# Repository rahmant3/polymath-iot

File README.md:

# Polymath-IoT

This project is a submission for the Climate Change Challenge hosted by Quicklogic Corp.: https://www.quicklogic.com/climate-change-challenge/

## Overview

Polymath-IoT is a generic sensor cluster consisting of two separate modules that connect together, a controller module and sensor module. The module is intended to be attached to a room and passively collect and publish data over BLE.

The controller module consists of a two-micro system, with the slave system acting as an IO expander, and the master module collecting the data and publishing it over BLE.

The sensor module simply contains all of the sensors for a particular sensor cluster, and connects to the controller module. For this competition our focus was on creating a sensor cluster for collecting air quality data.

## Directory Structure
- hardware -- Contains the schematic for the Polymath system, as well as the files needed to build the PCB for the system.
- quickfeather -- Contains the documentation and source code for the master controller of the Polymath system, hosted on a Quickfeather board.
- stm32 -- Contains the documentation and source code for the slave controller of the Polymath system, hosted on an STM32 micro.
- utils -- Contains utility scripts used to support this project, such as Python scripts used to obtain training data from the system over BLE.

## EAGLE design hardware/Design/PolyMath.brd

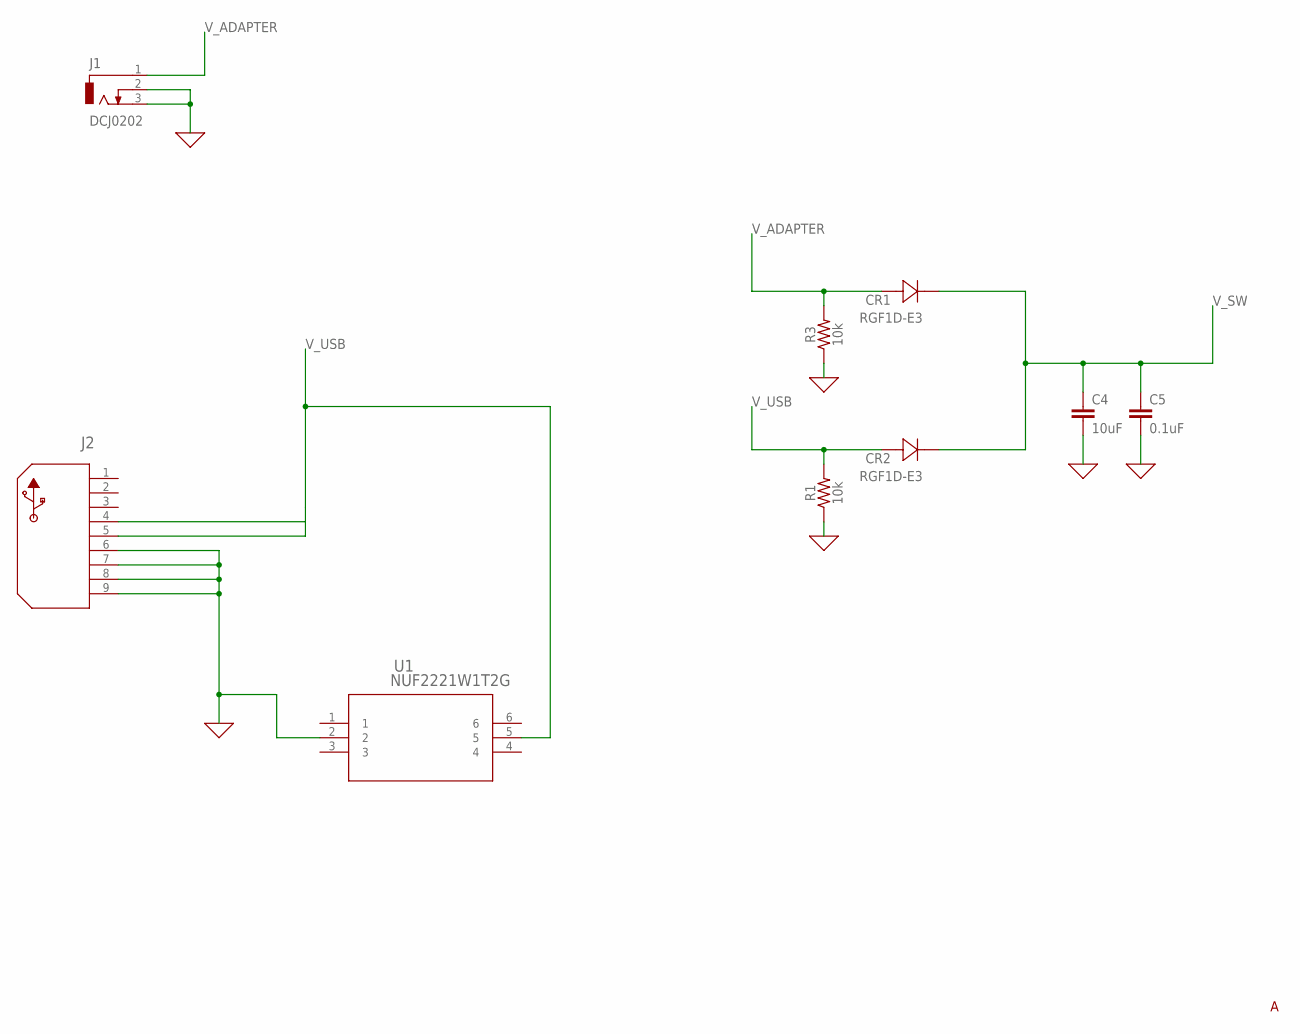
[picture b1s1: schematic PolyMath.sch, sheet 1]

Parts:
C4: 10uF; 0603
C5: 0.1uF; 0603
CR1, CR2: RGF1D-E3; DIODE_DO214BA
J1: DCJ0202
J2: 1734035-4; CONN5_USB1734035_TEC
R1, R3: 10k; 0603
U1: NUF2221W1T2G; SOIC6_SC70_1P35X2P2_ONS

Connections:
0: C4.2, C5.2, J1.2, J1.3, J2.6, J2.7, J2.8, J2.9, R1.1, R3.1, U1.2; also elsewhere on the board
V_ADAPTER: CR1.2, J1.1, R3.2
V_SW: C4.1, C5.1, CR1.1, CR2.1; also elsewhere on the board
V_USB: CR2.2, J2.4, J2.5, R1.2, U1.5

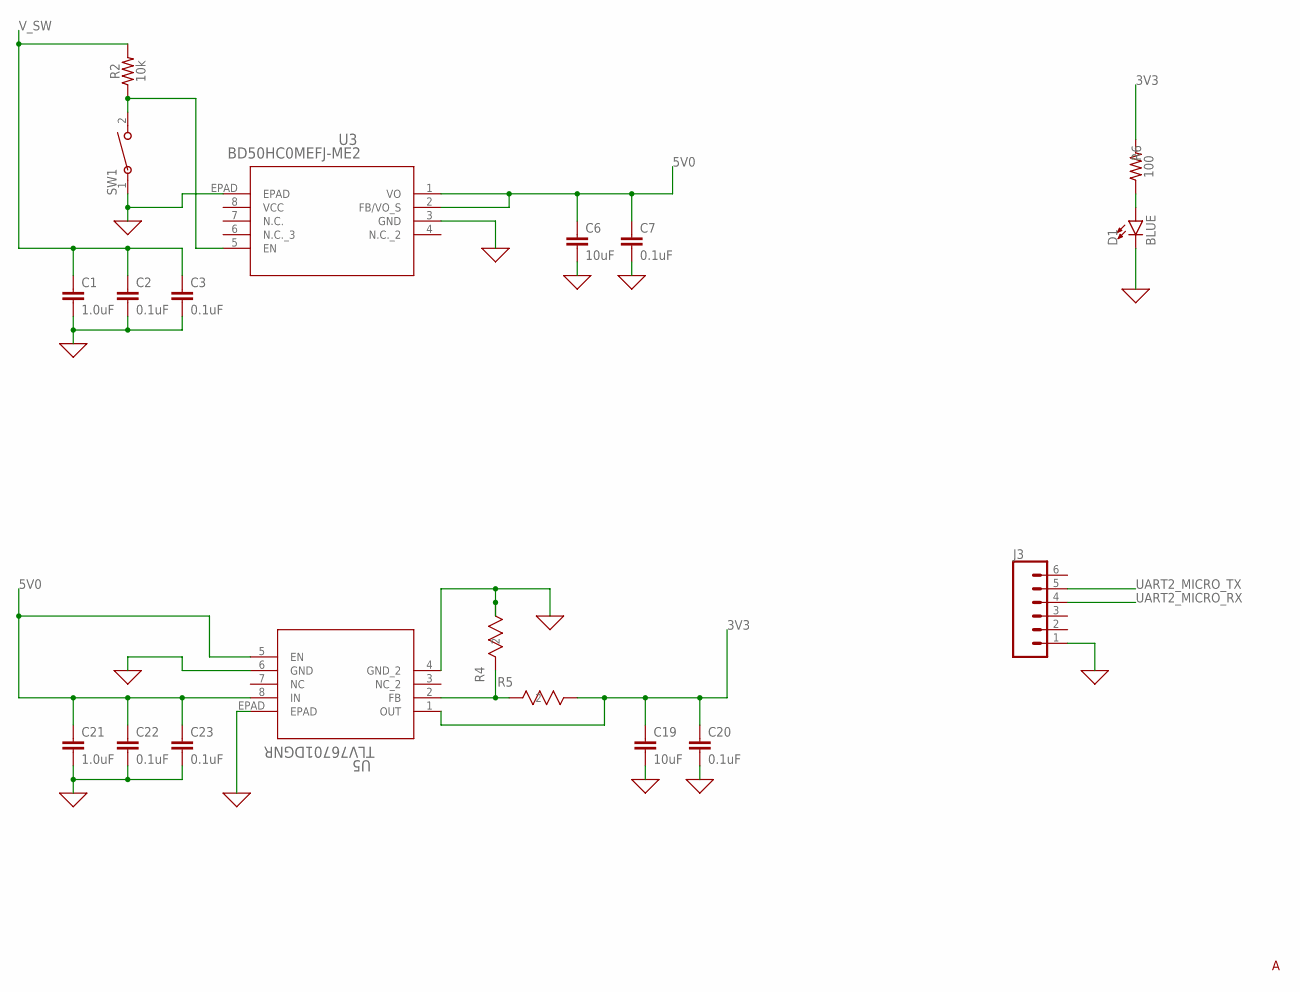
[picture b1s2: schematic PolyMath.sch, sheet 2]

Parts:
C1, C21: 1.0uF; 0603
C2, C3, C7, C20, C22, C23: 0.1uF; 0603
C6, C19: 10uF; 0603
D1: BLUE; LED-0603
J3: CONN_06NO_SILK_FEMALE_PTH; 1X06_NO_SILK
R2: 10k; 0603
R4: TNPW0603160KBEEA; RC0603N_VIS
R5: CRCW0603499KFKEA; RES_CRCW_0603
R6: 100; 0603
SW1: TL9320AF400QG; SW_TL9320_EWI
U3: BD50HC0MEFJ-ME2; HTSOP-J8_ROM
U5: TLV76701DGNR; SOIC_01DGNR_TEX

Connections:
0: C1.2, C2.2, C3.2, C6.2, C7.2, C19.2, C20.2, C21.2, C22.2, C23.2, D1.C, J3.1, R4.1, SW1.1, U3.3 (GND), U3.EPAD, U5.4 (GND_2), U5.6 (GND), U5.EPAD; also elsewhere on the board
3V3: C19.1, C20.1, R5.1, R6.2, U5.1 (OUT); also elsewhere on the board
5V0: C6.1, C7.1, C21.1, C22.1, C23.1, U3.1 (VO), U3.2 (FB/VO_S), U5.5 (EN), U5.8 (IN); also elsewhere on the board
unnamed: R2.1, SW1.2, U3.5 (EN)
unnamed: D1.A, R6.1
unnamed: R4.2, R5.2, U5.2 (FB)
UART2_MICRO_RX: J3.4; also elsewhere on the board
UART2_MICRO_TX: J3.5; also elsewhere on the board
VCC: U3.8 (VCC)
V_SW: C1.1, C2.1, C3.1, R2.2; also elsewhere on the board

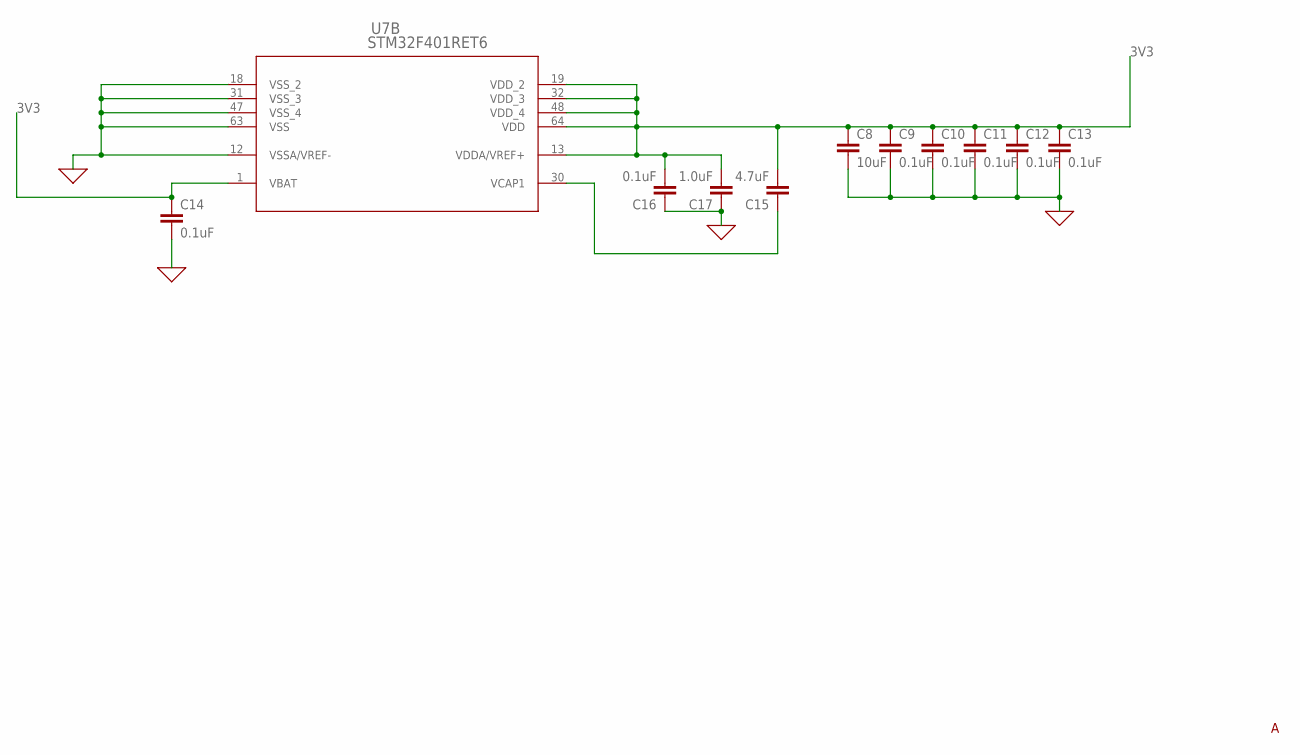
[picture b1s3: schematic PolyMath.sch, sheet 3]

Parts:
C8: 10uF; 0805
C9, C10, C11, C12, C13, C14, C16: 0.1uF; 0603
C15: 4.7uF; 0603
C17: 1.0uF; 0805
U7: STM32F401RET6; LQFP64-10X10MM

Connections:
0: C8.2, C9.2, C10.2, C11.2, C12.2, C13.2, C14.2, C16.1, C17.1, U7.12 (VSSA/VREF-), U7.18 (VSS_2), U7.31 (VSS_3), U7.47 (VSS_4), U7.63 (VSS); also elsewhere on the board
3V3: C8.1, C9.1, C10.1, C11.1, C12.1, C13.1, C14.1, C15.2, C16.2, C17.2, U7.1 (VBAT), U7.13 (VDDA/VREF+), U7.19 (VDD_2), U7.32 (VDD_3), U7.48 (VDD_4), U7.64 (VDD); also elsewhere on the board
unnamed: C15.1, U7.30 (VCAP1)

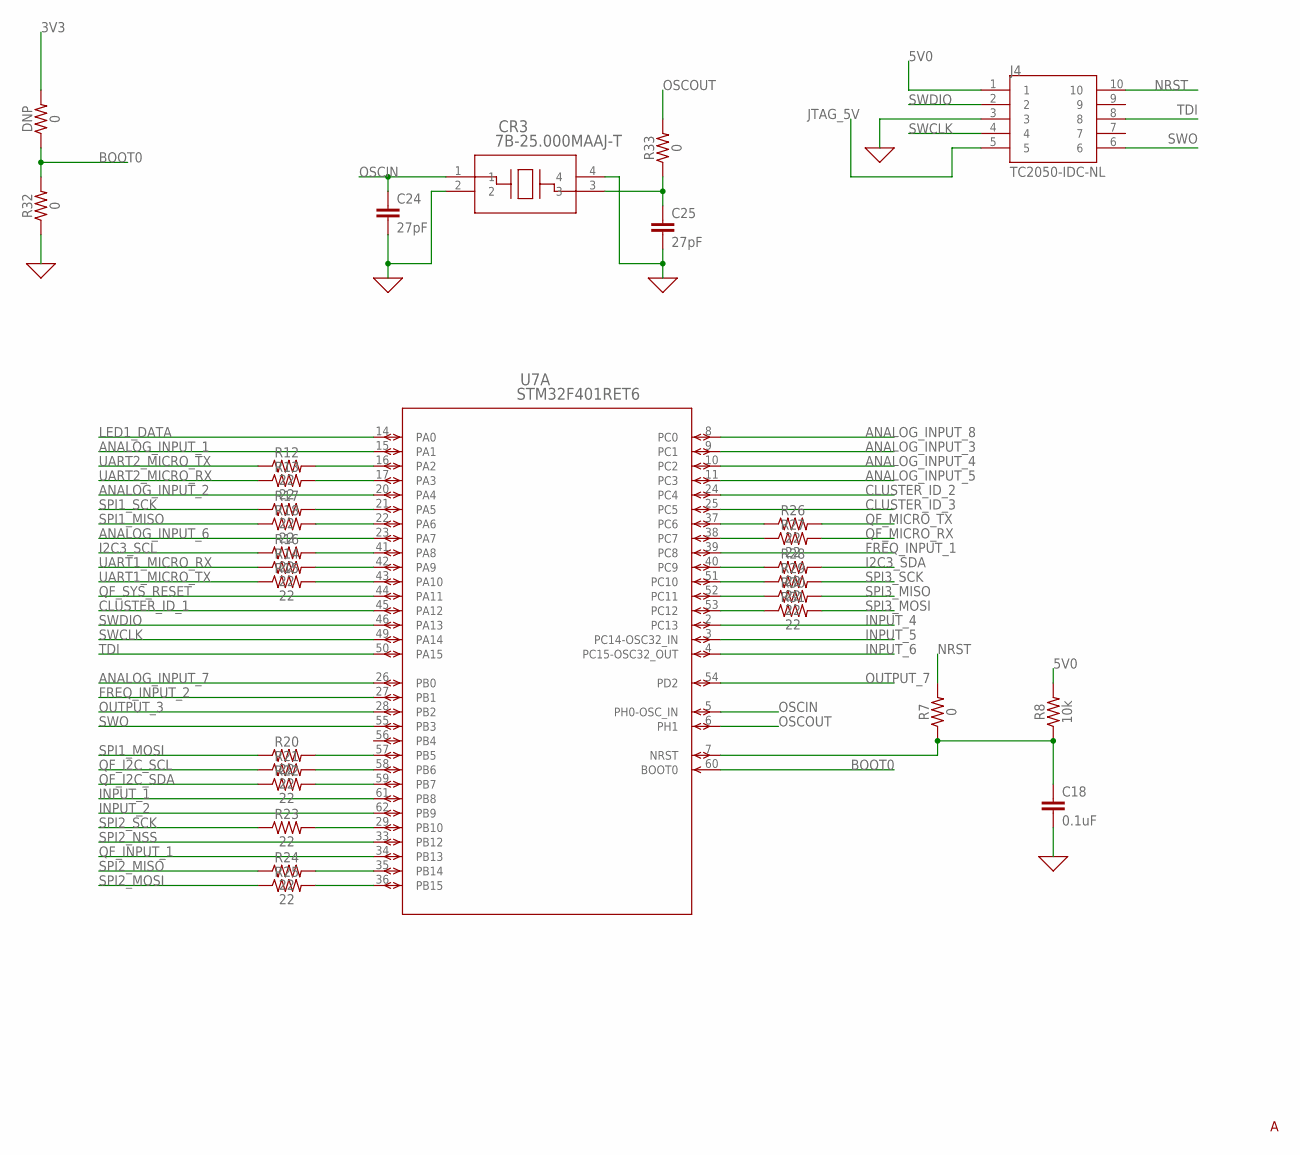
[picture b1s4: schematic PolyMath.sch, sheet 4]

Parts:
C18: 0.1uF; 0603
C24, C25: 27pF; 0603
CR3: 7B-25.000MAAJ-T; CRYSTAL_TXC_7B
DNP: 0; 0603
J4: TC2050-IDC-NL; TAG-CONNECT_TC2050-IDC-NL
R7, R32, R33: 0; 0603
R8: 10k; 0603
R12, R13, R14, R15, R16, R17, R18, R20, R21, R22, R23, R24, R25, R26, R27, R28, R29, R30, R31: 22; 0402
U7: STM32F401RET6; LQFP64-10X10MM

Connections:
0: C18.2, C24.2, C25.2, CR3.2, CR3.4, J4.3, R32.1; also elsewhere on the board
3V3: DNP.2; also elsewhere on the board
5V0: J4.1; also elsewhere on the board
ANALOG_INPUT_1: U7.15 (PA1); also elsewhere on the board
ANALOG_INPUT_2: U7.20 (PA4); also elsewhere on the board
ANALOG_INPUT_3: U7.9 (PC1); also elsewhere on the board
ANALOG_INPUT_4: U7.10 (PC2); also elsewhere on the board
ANALOG_INPUT_5: U7.11 (PC3); also elsewhere on the board
ANALOG_INPUT_6: U7.23 (PA7); also elsewhere on the board
ANALOG_INPUT_7: U7.26 (PB0); also elsewhere on the board
ANALOG_INPUT_8: U7.8 (PC0); also elsewhere on the board
BOOT0: DNP.1, R32.2, U7.60 (BOOT0)
CLUSTER_ID_1: U7.45 (PA12); also elsewhere on the board
CLUSTER_ID_2: U7.24 (PC4); also elsewhere on the board
CLUSTER_ID_3: U7.25 (PC5); also elsewhere on the board
FREQ_INPUT_1: U7.39 (PC8); also elsewhere on the board
FREQ_INPUT_2: U7.27 (PB1); also elsewhere on the board
I2C3_SCL: R16.1; also elsewhere on the board
I2C3_SDA: R28.2; also elsewhere on the board
INPUT_1: U7.61 (PB8); also elsewhere on the board
INPUT_2: U7.62 (PB9); also elsewhere on the board
INPUT_4: U7.2 (PC13); also elsewhere on the board
INPUT_5: U7.3 (PC14-OSC32_IN); also elsewhere on the board
INPUT_6: U7.4 (PC15-OSC32_OUT)
JTAG_5V: J4.5
LED1_DATA: U7.14 (PA0); also elsewhere on the board
unnamed: C18.1, R7.1, R8.1, U7.7 (NRST)
unnamed: C25.1, CR3.3, R33.1
unnamed: R12.2, U7.16 (PA2)
unnamed: R13.2, U7.17 (PA3)
unnamed: R14.2, U7.42 (PA9)
unnamed: R15.2, U7.43 (PA10)
unnamed: R16.2, U7.41 (PA8)
unnamed: R17.2, U7.21 (PA5)
unnamed: R18.2, U7.22 (PA6)
unnamed: R20.2, U7.57 (PB5)
unnamed: R21.2, U7.58 (PB6)
unnamed: R22.2, U7.59 (PB7)
unnamed: R23.2, U7.29 (PB10)
unnamed: R24.2, U7.35 (PB14)
unnamed: R25.2, U7.36 (PB15)
unnamed: R26.1, U7.37 (PC6)
unnamed: R27.1, U7.38 (PC7)
unnamed: R28.1, U7.40 (PC9)
unnamed: R29.1, U7.51 (PC10)
unnamed: R30.1, U7.52 (PC11)
unnamed: R31.1, U7.53 (PC12)
NRST: J4.10, R7.2
OSCIN: C24.1, CR3.1, U7.5 (PH0-OSC_IN)
OSCOUT: R33.2, U7.6 (PH1)
OUTPUT_3: U7.28 (PB2); also elsewhere on the board
OUTPUT_7: U7.54 (PD2); also elsewhere on the board
QF_I2C_SCL: R21.1; also elsewhere on the board
QF_I2C_SDA: R22.1; also elsewhere on the board
QF_INPUT_1: U7.34 (PB13); also elsewhere on the board
QF_MICRO_RX: R27.2; also elsewhere on the board
QF_MICRO_TX: R26.2; also elsewhere on the board
QF_SYS_RESET: U7.44 (PA11); also elsewhere on the board
SPI1_MISO: R18.1; also elsewhere on the board
SPI1_MOSI: R20.1; also elsewhere on the board
SPI1_SCK: R17.1; also elsewhere on the board
SPI2_MISO: R24.1; also elsewhere on the board
SPI2_MOSI: R25.1; also elsewhere on the board
SPI2_NSS: U7.33 (PB12); also elsewhere on the board
SPI2_SCK: R23.1; also elsewhere on the board
SPI3_MISO: R30.2; also elsewhere on the board
SPI3_MOSI: R31.2; also elsewhere on the board
SPI3_SCK: R29.2; also elsewhere on the board
SWCLK: J4.4, U7.49 (PA14)
SWDIO: J4.2, U7.46 (PA13)
SWO: J4.6, U7.55 (PB3)
TDI: J4.8, U7.50 (PA15)
UART1_MICRO_RX: R14.1; also elsewhere on the board
UART1_MICRO_TX: R15.1; also elsewhere on the board
UART2_MICRO_RX: R13.1; also elsewhere on the board
UART2_MICRO_TX: R12.1; also elsewhere on the board

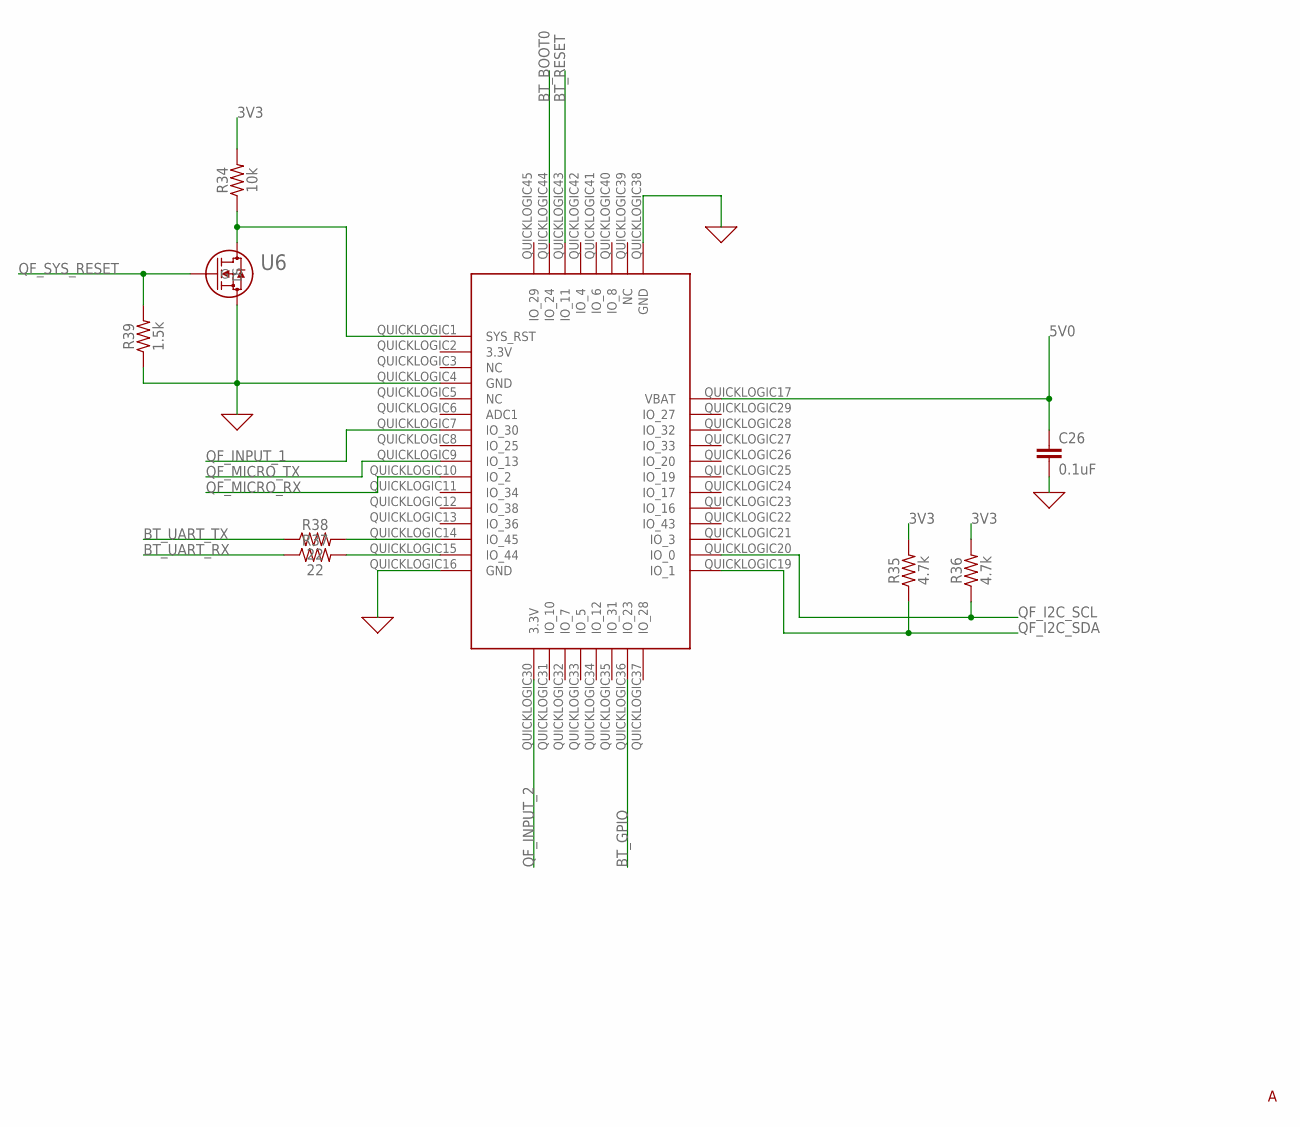
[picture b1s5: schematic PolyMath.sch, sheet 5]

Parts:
C26: 0.1uF; 0603
R34: 10k; 0603
R35, R36: 4.7k; 0603
R37, R38: 22; 0402
R39: 1.5k; 0603
U6: DMN65D8L-7SOT-23_2P9X1P3_DIO-M; SOT-23_2P9X1P3_DIO-M
U$1: QUICKFEATHER; QUICKLOGIC

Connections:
0: C26.2, R39.1, U6.3 (S), U$1.QUICKLOGIC4 (GND), U$1.QUICKLOGIC16 (GND), U$1.QUICKLOGIC38 (GND); also elsewhere on the board
3V3: R34.2, R35.2, R36.2; also elsewhere on the board
5V0: C26.1, U$1.QUICKLOGIC17 (VBAT); also elsewhere on the board
BT_BOOT0: U$1.QUICKLOGIC44 (IO_24); also elsewhere on the board
BT_GPIO: U$1.QUICKLOGIC36 (IO_23); also elsewhere on the board
BT_RESET: U$1.QUICKLOGIC43 (IO_11); also elsewhere on the board
BT_UART_RX: R37.1; also elsewhere on the board
BT_UART_TX: R38.1; also elsewhere on the board
unnamed: R34.1, U6.2 (D), U$1.QUICKLOGIC1 (SYS_RST)
unnamed: R38.2, U$1.QUICKLOGIC14 (IO_45)
unnamed: R37.2, U$1.QUICKLOGIC15 (IO_44)
QF_I2C_SCL: R36.1, U$1.QUICKLOGIC20 (IO_0); also elsewhere on the board
QF_I2C_SDA: R35.1, U$1.QUICKLOGIC19 (IO_1); also elsewhere on the board
QF_INPUT_1: U$1.QUICKLOGIC7 (IO_30); also elsewhere on the board
QF_INPUT_2: U$1.QUICKLOGIC30 (3.3V)
QF_MICRO_RX: U$1.QUICKLOGIC10 (IO_2); also elsewhere on the board
QF_MICRO_TX: U$1.QUICKLOGIC9 (IO_13); also elsewhere on the board
QF_SYS_RESET: R39.2, U6.1 (G); also elsewhere on the board

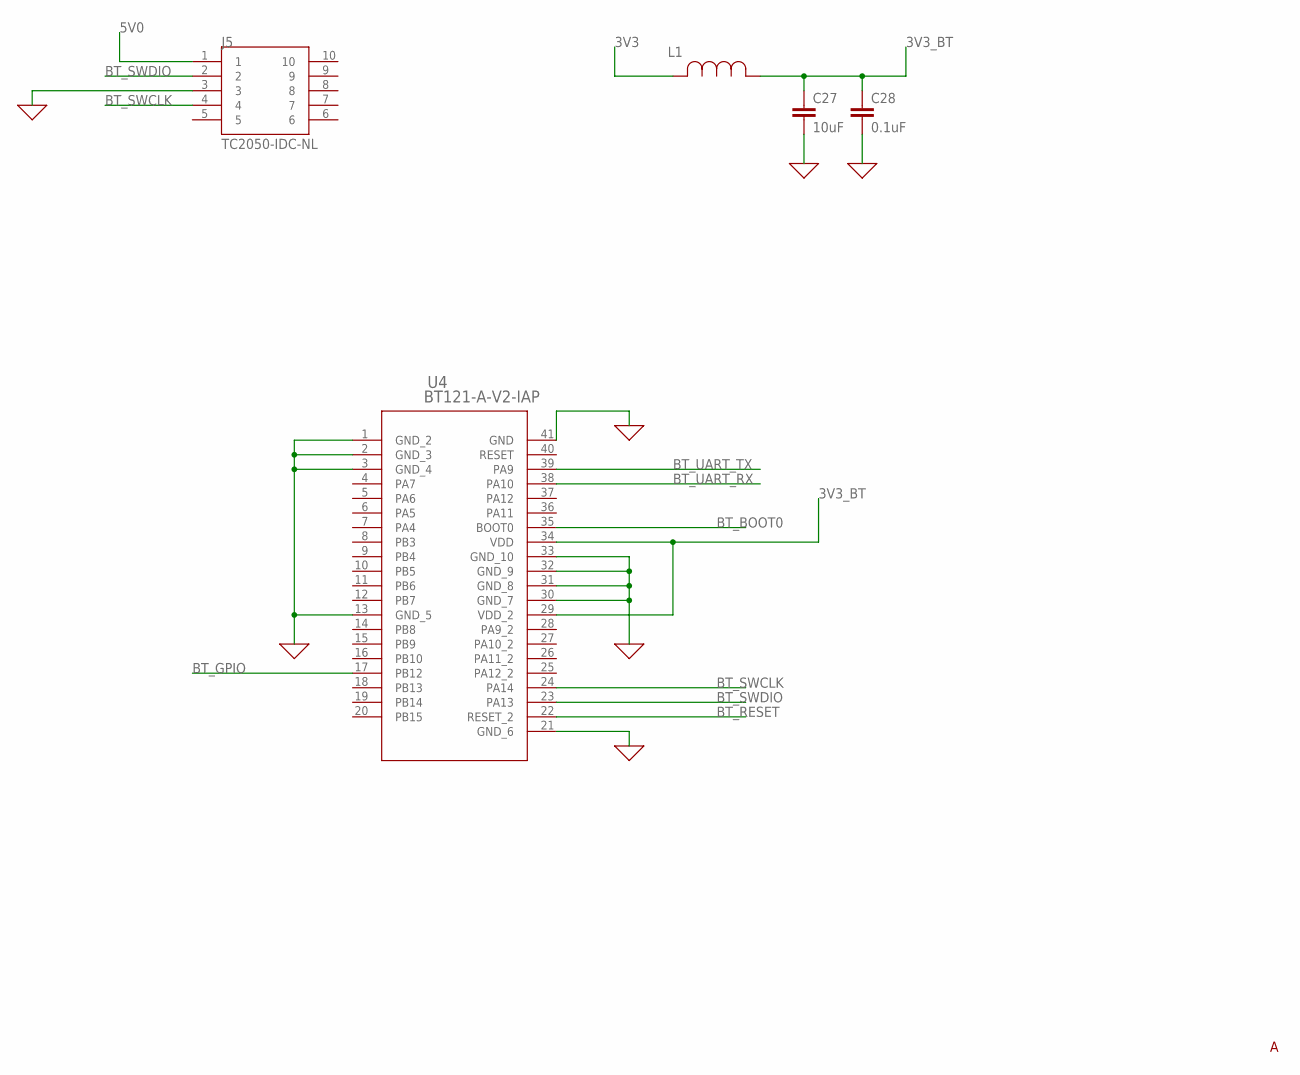
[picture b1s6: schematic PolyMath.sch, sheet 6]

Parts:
C27: 10uF; 0603
C28: 0.1uF; 0603
J5: TC2050-IDC-NL; TAG-CONNECT_TC2050-IDC-NL
L1: MMZ1608Y121BTA00IND_1608_TDK-L; IND_1608_TDK-L
U4: BT121-A-V2-IAP; SMD41_13P9X11_SIL

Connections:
0: C27.2, C28.2, J5.3, U4.1 (GND_2), U4.2 (GND_3), U4.3 (GND_4), U4.13 (GND_5), U4.21 (GND_6), U4.30 (GND_7), U4.31 (GND_8), U4.32 (GND_9), U4.33 (GND_10), U4.41 (GND); also elsewhere on the board
3V3: L1.2; also elsewhere on the board
3V3_BT: C27.1, C28.1, L1.1, U4.29 (VDD_2), U4.34 (VDD)
5V0: J5.1; also elsewhere on the board
BT_BOOT0: U4.35 (BOOT0); also elsewhere on the board
BT_GPIO: U4.17 (PB12); also elsewhere on the board
BT_RESET: U4.22 (RESET_2); also elsewhere on the board
BT_SWCLK: J5.4, U4.24 (PA14)
BT_SWDIO: J5.2, U4.23 (PA13)
BT_UART_RX: U4.38 (PA10); also elsewhere on the board
BT_UART_TX: U4.39 (PA9); also elsewhere on the board

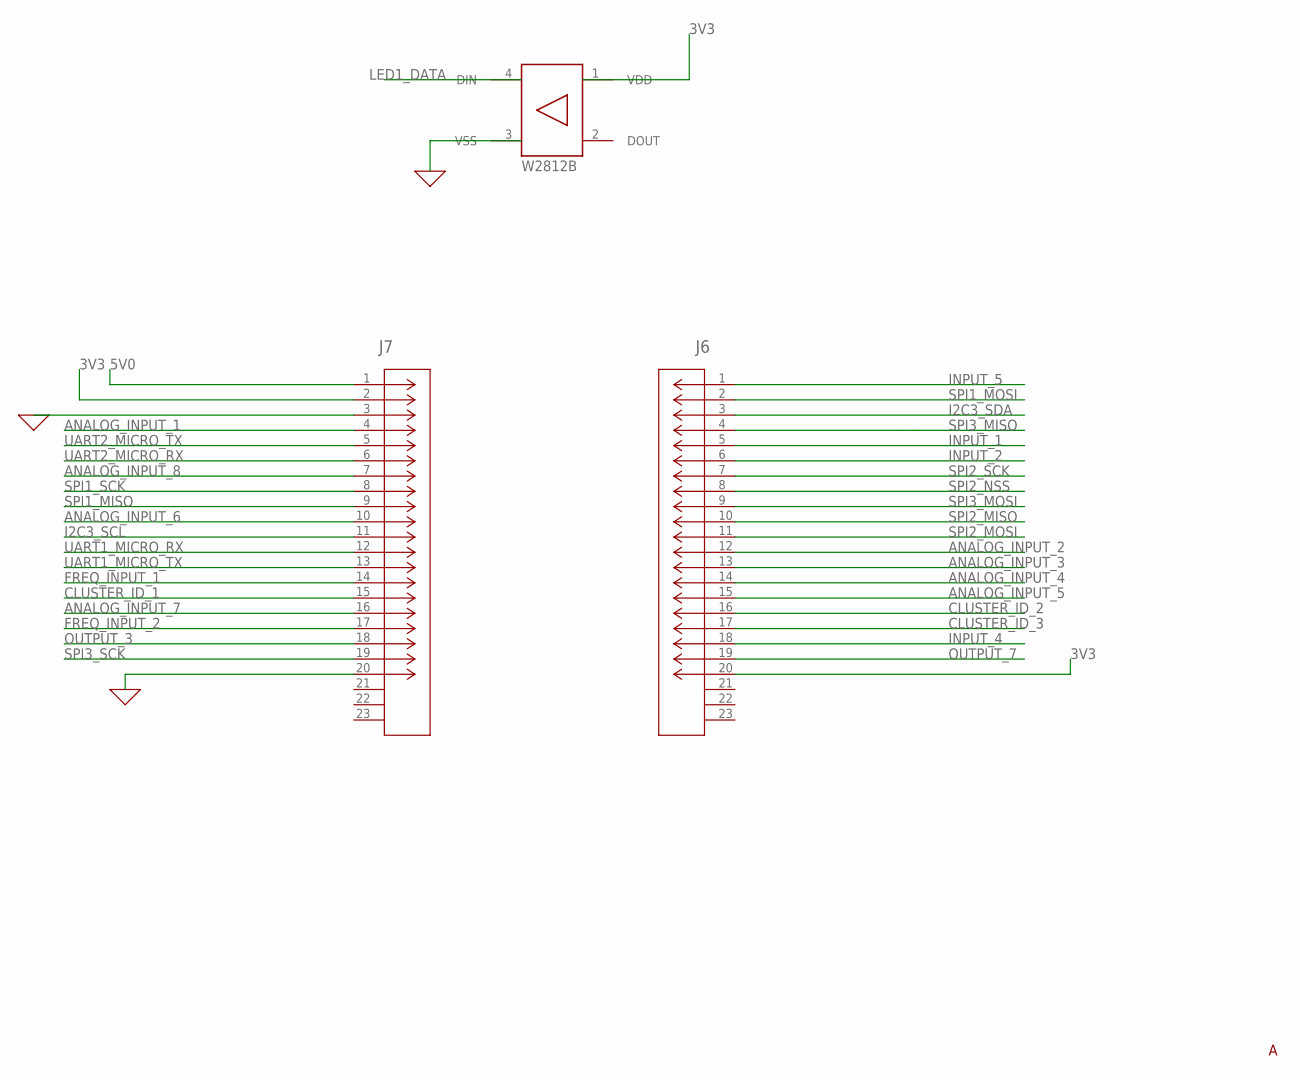
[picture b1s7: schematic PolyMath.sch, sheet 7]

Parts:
J6, J7: 104074-4; CONN20_104074_28P7X11P18_TEC
U$2: WS2812B

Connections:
0: J7.3, J7.20, U$2.3 (VSS); also elsewhere on the board
3V3: J6.20, J7.2, U$2.1 (VDD); also elsewhere on the board
5V0: J7.1; also elsewhere on the board
ANALOG_INPUT_1: J7.4; also elsewhere on the board
ANALOG_INPUT_2: J6.12; also elsewhere on the board
ANALOG_INPUT_3: J6.13; also elsewhere on the board
ANALOG_INPUT_4: J6.14; also elsewhere on the board
ANALOG_INPUT_5: J6.15; also elsewhere on the board
ANALOG_INPUT_6: J7.10; also elsewhere on the board
ANALOG_INPUT_7: J7.16; also elsewhere on the board
ANALOG_INPUT_8: J7.7; also elsewhere on the board
CLUSTER_ID_1: J7.15; also elsewhere on the board
CLUSTER_ID_2: J6.16; also elsewhere on the board
CLUSTER_ID_3: J6.17; also elsewhere on the board
FREQ_INPUT_1: J7.14; also elsewhere on the board
FREQ_INPUT_2: J7.17; also elsewhere on the board
I2C3_SCL: J7.11; also elsewhere on the board
I2C3_SDA: J6.3; also elsewhere on the board
INPUT_1: J6.5; also elsewhere on the board
INPUT_2: J6.6; also elsewhere on the board
INPUT_4: J6.18; also elsewhere on the board
INPUT_5: J6.1; also elsewhere on the board
LED1_DATA: U$2.4 (DIN); also elsewhere on the board
OUTPUT_3: J7.18; also elsewhere on the board
OUTPUT_7: J6.19; also elsewhere on the board
SPI1_MISO: J7.9; also elsewhere on the board
SPI1_MOSI: J6.2; also elsewhere on the board
SPI1_SCK: J7.8; also elsewhere on the board
SPI2_MISO: J6.10; also elsewhere on the board
SPI2_MOSI: J6.11; also elsewhere on the board
SPI2_NSS: J6.8; also elsewhere on the board
SPI2_SCK: J6.7; also elsewhere on the board
SPI3_MISO: J6.4; also elsewhere on the board
SPI3_MOSI: J6.9; also elsewhere on the board
SPI3_SCK: J7.19; also elsewhere on the board
UART1_MICRO_RX: J7.12; also elsewhere on the board
UART1_MICRO_TX: J7.13; also elsewhere on the board
UART2_MICRO_RX: J7.6; also elsewhere on the board
UART2_MICRO_TX: J7.5; also elsewhere on the board

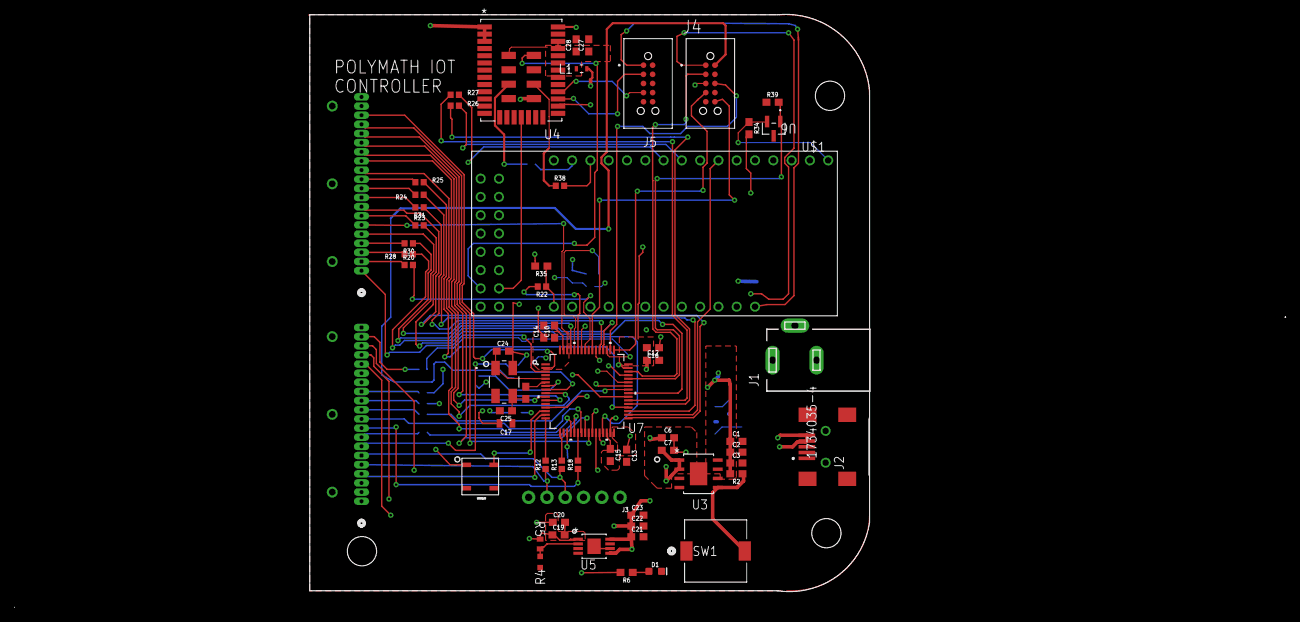
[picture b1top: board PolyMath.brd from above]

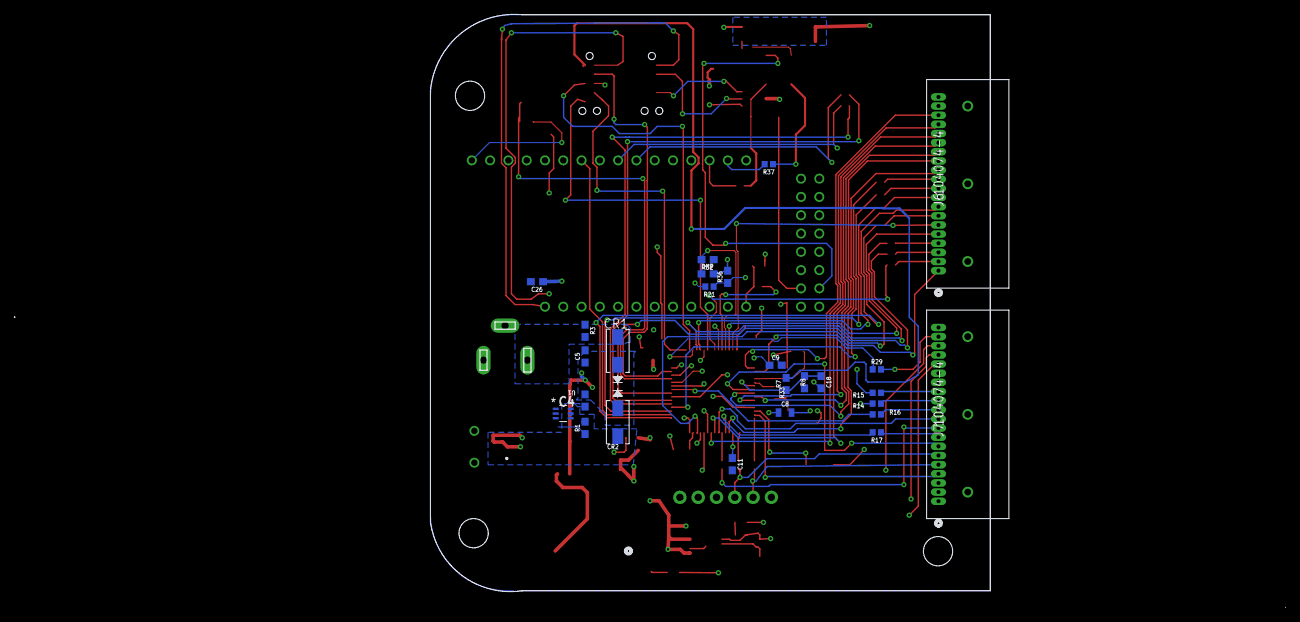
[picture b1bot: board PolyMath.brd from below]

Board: 4 copper layers, 176.5 x 82.3 mm, 85 parts (26 on the bottom side), 92 nets.

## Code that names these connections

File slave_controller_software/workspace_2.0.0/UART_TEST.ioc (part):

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PA2.GPIO_PuPd=GPIO_NOPULL
Mcu.UserName=STM32F401RETx
PA14.GPIO_Label=TCK
PA3.GPIO_PuPd=GPIO_NOPULL
PA2.GPIO_Speed=GPIO_SPEED_FREQ_LOW
PA3.GPIOParameters=GPIO_Speed,GPIO_PuPd,GPIO_Label,GPIO_Mode
PA3.GPIO_Speed=GPIO_SPEED_FREQ_LOW
PA2.GPIOParameters=GPIO_Speed,GPIO_PuPd,GPIO_Label,GPIO_Mode
RCC.SYSCLKSource=RCC_SYSCLKSOURCE_PLLCLK
PA12.Signal=GPIO_Input
PH0\ -\ OSC_IN.Signal=RCC_OSC_IN
PB6.Signal=I2C1_SCL
PC7.Signal=USART6_RX
PB6.Mode=I2C
RCC.HSE_VALUE=8000000
PC13-ANTI_TAMP.Signal=GPXTI13
PC14-OSC32_IN.Mode=LSE-External-Oscillator
PA14.Mode=Serial_Wire
PA5.GPIO_PuPd=GPIO_NOPULL
PB3.GPIOParameters=GPIO_Label
PB7.Signal=I2C1_SDA
PA13.GPIOParameters=GPIO_Label
Mcu.Package=LQFP64
PA2.GPIO_Label=USART_TX
PA10.Signal=USART1_RX
PA5.GPIOParameters=GPIO_Speed,GPIO_PuPd,GPIO_Label,GPIO_Mode
PC5.Signal=GPIO_Input
PA3.Signal=USART2_RX
PC13-ANTI_TAMP.GPIOParameters=GPIO_PuPd,GPIO_Label,GPIO_ModeDefaultEXTI
PA2.GPIO_Mode=GPIO_MODE_AF_PP
PB3.GPIO_Label=SWO
PC15-OSC32_OUT.Mode=LSE-External-Oscillator
PA10.Mode=Asynchronous
PC13-ANTI_TAMP.GPIO_PuPd=GPIO_NOPULL
PC13-ANTI_TAMP.GPIO_Label=B1 [Blue PushButton]
PH1\ -\ OSC_OUT.Mode=HSE-External-Clock-Source
PC4.Signal=GPIO_Input
PC6.Signal=USART6_TX
PC14-OSC32_IN.Signal=RCC_OSC32_IN
boardIOC=true
PA13.Signal=SYS_JTMS-SWDIO
PA3.Mode=Asynchronous
PA9.Mode=Asynchronous
PH0\ -\ OSC_IN.Mode=HSE-External-Clock-Source
PA3.GPIO_Mode=GPIO_MODE_AF_PP
PC6.Mode=Asynchronous
PA9.Signal=USART1_TX
PC15-OSC32_OUT.Signal=RCC_OSC32_OUT
PA5.Signal=GPIO_Output
PH1\ -\ OSC_OUT.Signal=RCC_OSC_OUT
board=NUCLEO-F401RE
PA13.Mode=Serial_Wire
Mcu.Name=STM32F401R(D-E)Tx
PA13.GPIO_Label=TMS
PA2.Signal=USART2_TX
PB3.Signal=SYS_JTDO-SWO
RCC.SYSCLKFreq_VALUE=84000000
PA5.GPIO_Label=LD2 [Green Led]
PA14.GPIOParameters=GPIO_Label
PC13-ANTI_TAMP.GPIO_ModeDefaultEXTI=GPIO_MODE_IT_FALLING
PB7.Mode=I2C
PA14.Signal=SYS_JTCK-SWCLK
PA5.GPIO_Speed=GPIO_SPEED_FREQ_LOW
PA2.Mode=Asynchronous
PC7.Mode=Asynchronous
PA5.GPIO_Mode=GPIO_MODE_OUTPUT_PP
PA3.GPIO_Label=USART_RX

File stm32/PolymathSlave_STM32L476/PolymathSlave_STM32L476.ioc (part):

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PA2.GPIO_PuPd=GPIO_NOPULL
Mcu.UserName=STM32L476RGTx
PB10.Mode=I2C
PH0-OSC_IN\ (PH0).Signal=RCC_OSC_IN
PA3.GPIO_PuPd=GPIO_NOPULL
PA2.GPIO_Speed=GPIO_SPEED_FREQ_VERY_HIGH
PA3.GPIOParameters=GPIO_Speed,GPIO_PuPd,GPIO_Label,GPIO_Mode
PC13.GPIO_Label=B1 [Blue PushButton]
PA3.GPIO_Speed=GPIO_SPEED_FREQ_VERY_HIGH
PB11.Signal=I2C2_SDA
PA2.GPIOParameters=GPIO_Speed,GPIO_PuPd,GPIO_Label,GPIO_Mode
RCC.SYSCLKSource=RCC_SYSCLKSOURCE_PLLCLK
PB3\ (JTDO-TRACESWO).Signal=SYS_JTDO-SWO
PA14\ (JTCK-SWCLK).Signal=SYS_JTCK-SWCLK
PA14\ (JTCK-SWCLK).GPIOParameters=GPIO_Label
RCC.HSE_VALUE=8000000
PA6.GPIO_PuPd=GPIO_PULLDOWN
PA5.GPIO_PuPd=GPIO_NOPULL
PC13.GPIO_PuPd=GPIO_NOPULL
Mcu.Package=LQFP64
PB9.Signal=I2C1_SDA
PA6.Signal=S_TIM3_CH1
PA2.GPIO_Label=USART_TX
PA10.Signal=USART1_RX
PA5.GPIOParameters=GPIO_Speed,GPIO_PuPd,GPIO_Label,GPIO_ModeDefaultOutputPP
PA13\ (JTMS-SWDIO).Signal=SYS_JTMS-SWDIO
PA13\ (JTMS-SWDIO).GPIOParameters=GPIO_Label
PA3.Signal=USART2_RX
PA2.GPIO_Mode=GPIO_MODE_AF_PP
PA6.GPIOParameters=GPIO_PuPd
PA14\ (JTCK-SWCLK).Mode=Serial_Wire
PA10.Mode=Asynchronous
PC13.Signal=GPXTI13
PC15-OSC32_OUT\ (PC15).Signal=RCC_OSC32_OUT
PA14\ (JTCK-SWCLK).GPIO_Label=TCK
PB3\ (JTDO-TRACESWO).GPIO_Label=SWO
boardIOC=true
PH1-OSC_OUT\ (PH1).Signal=RCC_OSC_OUT
PA3.Mode=Asynchronous
PA9.Mode=Asynchronous
PB11.Mode=I2C
PA3.GPIO_Mode=GPIO_MODE_AF_PP
PB9.Mode=I2C
PA9.Signal=USART1_TX
PB10.Signal=I2C2_SCL
PA5.Signal=GPIO_Output
board=NUCLEO-L476RG
PB3\ (JTDO-TRACESWO).GPIOParameters=GPIO_Label
PA13\ (JTMS-SWDIO).GPIO_Label=TMS
PA5.GPIO_ModeDefaultOutputPP=GPIO_MODE_OUTPUT_PP
PC13.GPIOParameters=GPIO_PuPd,GPIO_Label,GPIO_ModeDefaultEXTI
Mcu.Name=STM32L476R(C-E-G)Tx
PA2.Signal=USART2_TX
PA13\ (JTMS-SWDIO).Mode=Serial_Wire
RCC.SYSCLKFreq_VALUE=80000000
PA5.GPIO_Label=LD2 [green Led]
PC13.GPIO_ModeDefaultEXTI=GPIO_MODE_IT_FALLING
PC14-OSC32_IN\ (PC14).Signal=RCC_OSC32_IN
PA5.GPIO_Speed=GPIO_SPEED_FREQ_LOW
PB8.Mode=I2C
PA2.Mode=Asynchronous
PB8.Signal=I2C1_SCL
PA3.GPIO_Label=USART_RX

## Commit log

2021-01-16 Create baseline app and SDK folders.
2021-01-16 Commit missing s3-gateware files.
2021-01-16 Updated to build properly.
2021-01-16 Created README.md.
2021-01-24 Created a revision of pm_protocol.h.
2021-01-24 Switch to the last tested GCC toolchain, to minimize risk of incompatibilities with the SDK.
2021-01-24 Ignore build artifacts.
2021-01-24 Added Python ignores.
2021-01-24 Added script and source to perform programming with TinyFPGA.
2021-01-24 Created VSCode task with a default task that can build the app in VSCode WSL.
2021-01-24 Try enabling the DEBUG USB UART.
2021-02-07 Updates to support development on Eclipse.
2021-02-07 Additional updates to support Eclipse builds.
2021-02-07 Update eclipse_build.bat to handle cleaning.
2021-02-21 Setup infrastructure for supporting custom CLI commands for Polymath.
2021-02-26 Additional changes to support using USBSERIAL as the data capture port.
    The reliability of the USBSERIAL is improved due to this forum post: https://forum.quicklogic.com/viewtopic.php?f=9&t=95
2021-02-27 Enough functionality to use USBSERIAL for both CLI and data capture.
2021-03-27 Clear app folder in order to restart with fpga uart project.
2021-03-27 Commit baseline with fpga-uart project.
2021-03-27 Update to properly build fpga-uart project.
2021-03-27 Enough support to build FPGA project from qorc-sdk folder.
2021-03-27 Commit fUART pga IP project from qorc-sdk.
2021-03-27 Build support for FPGA project.
2021-03-27 Update makefile to work with FPGA bitstream header file.
2021-03-27 Change one FPGA UART to IO_2, IO_13.
2021-04-02 Initial implementation of pm_protocol.h.
2021-04-03 Implement pm_core module.
2021-04-03 Added eclipse_build.bat.
2021-04-03 Improvements to pm_protocol module.
2021-04-03 Correction to pm_core.c implementation.
2021-04-03 Slave SW TEST
    Added Slave SW for UART TEST
2021-04-03 QF UART test with hard uart.
2021-04-04 Successful test with pm_protocol loopback test.
2021-04-04 Bugfixes to pm_protocol.c
2021-04-04 Enhancements to pm_protocol to handle decoding and encoding raw packets.
2021-04-04 Add ack after receiving the first two bytes.
2021-04-10 Bugfixes and additional tests.
2021-04-17 Preliminary bt121 testing.
2021-04-17 Initial nrf51 working code.
2021-04-17 Added functionality for BLE over UART RX.
2021-04-18 Successful bluetooth tests with Mock Air Cluster implementation.
2021-04-18 Added BME680 files
2021-04-24 Added initial training code.
2021-04-24 Added slave code for STM32L476 NUCLEO board.
2021-04-24 Added more code to support training.
2021-04-24 Added BME680 updates.
2021-05-02 Added support for collecting training data.
2021-05-02 Updates to support collecting training data.
2021-05-02 Added hardware files from SLAVE_UART_TEST.
2021-05-16 Added MICS
2021-05-16 refactor
2021-05-30 Updated Design files
2021-05-30 Updated slave controller software and documentation.

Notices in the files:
parts and their libraries:
SparkFun-Capacitors: Licensing: Creative Commons ShareAlike 4.0 International - https://creativecommons.org/licenses/by-sa/4.0
COPYRIGHT: Copyright (C) 2016 Accelerated Designs. All rights reserved
COPYRIGHT: Copyright (C) 2018 Accelerated Designs. All rights reserved
